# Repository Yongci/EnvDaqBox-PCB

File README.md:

# EnvDaQ Box

This is a development board designed for automated flower watering or smart agriculture, primarily used for controlling the watering and lighting systems. It is currently under development.
The development board utilizes Espressif Systems' ESP32-C6 as the main controller. This SoC is based on the RISC-V architecture core and supports ultra-low power consumption and WiFi-6 (802.11ax).

## 3D model

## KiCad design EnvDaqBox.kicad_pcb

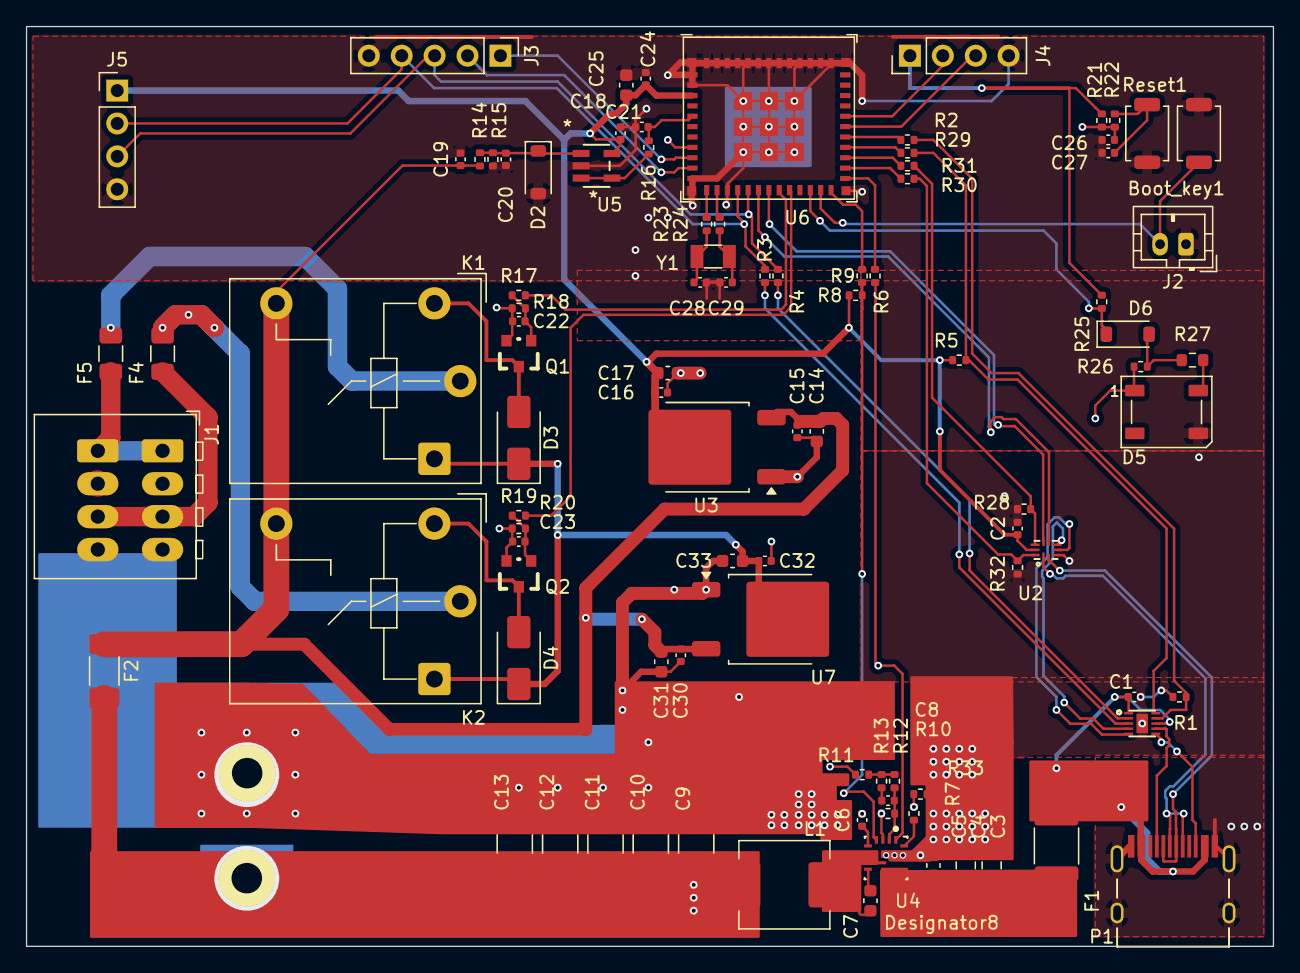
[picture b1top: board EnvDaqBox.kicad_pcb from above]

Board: 4 copper layers, 96.2 x 71.0 mm, 96 parts (0 on the bottom side), 66 nets.

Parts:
Boot_key1: SW_Push; SW_SPST_TS-1088-xR020
C1, C19: 1uF/50V(10%); C_0402_1005Metric
C2, C15, C16, C18, C20, C22, C23, C24, C27, C31, C32: 0.1uF/50V(10%); C_0402_1005Metric
C3, C4: 10uF/50V(20%); C_0805_2012Metric
C5, C7: 0.1uF/50V(10%); C_0603_1608Metric
C6: 47nF/50V(10%); C_0402_1005Metric
C8: 47pF/50V(10%); C_0402_1005Metric
C9, C10, C11, C12, C13: 22uF/25V(10%); C_1210_3225Metric
C14, C17, C25, C30, C33: 10uF/25V(20%); C_0603_1608Metric
C21: 0.1uF/6V(10%); C_0402_1005Metric
C26: 1uF; C_0402_1005Metric
C28, C29: 12pF; C_0402_1005Metric
D2: BZT52C3V3; D_SOD-123
D3, D4: 1N4007; D_SMA
D5: WS2812B; LED_WS2812B_PLCC4_5.0x5.0mm_P3.2mm
D6: 1N4148W; D_SOD-123
F1: 5A/33V; Fuse_1812_4532Metric
F2: 15A; C_1808_4520Metric
F4, F5: 5A/16V; Fuse_1206_3216Metric
J1: Screw_Terminal_01x04; TerminalBlock_WAGO_233-504_2x04_P2.54mm
J2: Conn_01x02_Pin; JST_PH_B2B-PH-K_1x02_P2.00mm_Vertical
J3: Conn_01x05_Pin; PinHeader_1x05_P2.54mm_Vertical
J4, J5: Conn_01x04_Pin; PinHeader_1x04_P2.54mm_Vertical
K1, K2: JQC-3FF-005-1H; Relay_SPST_Hongfa_JQC-3FF_0XX-1H
L1: 5.6uH; L_APV_APH0650
P1: TYPE-C-Receptacle-2.0
Q1, Q2: S8050; SOT-23
R1: 56k(1%); R_0402_1005Metric
R2, R3, R4, R6, R9, R11, R13, R22, R29, R30, R31, R33: 0; R_0402_1005Metric
R5, R8, R21, R28, R32: 10k; R_0402_1005Metric
R7: 52.3k(1%); R_0402_1005Metric
R10: 20k(1%); R_0402_1005Metric
R12: 400k(1%); R_0402_1005Metric
R14: 120k(1%); R_0402_1005Metric
R15: 43k(1%); R_0402_1005Metric
R16, R17, R19: 1k(1%); R_0402_1005Metric
R18, R20: 5.1k(1%); R_0402_1005Metric
R23, R24: 0(1%); R_0402_1005Metric
R25: 3.3k(1%); R_0402_1005Metric
R26: 10k(1%); R_0402_1005Metric
R27: 0(1%); R_0603_1608Metric
Reset1: SW_Push; SW_SPST_TS-1088-xR020
U1: CH224Q; DFN10_2X2
U2: CH9442Q; QFN10_14X18
U3: SGM2212-3.3XOB2G/TR; TO-252-2
U4: TPS56A37RPAR; RPA0010A-MFG
U5: TSU111HYLT; SOT23-5_STM
U6: ESP32-C6-MINI-1U
U7: SGM2212-5.0XOB2G/TR; TO-252-2
Y1: 32kHz; Crystal_SMD_3215-2Pin_3.2x1.5mm

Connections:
/BAT_VREF: C21.2, R16.1, U6.5 (IO2)
/BUCK_EN: R6.1, U6.25 (IO19)
/BUCK_PG: R9.1, U6.24 (IO18)
/CFG1: R2.1, U6.29 (IO23)
/CH_USB_N: U1.5 (DM), U2.4 (S0B)
/CH_USB_P: U1.4 (DP), U2.5 (S0A)
/EN: R31.1, U6.27 (IO21)
/ESP32USB_N: U2.6 (S1B), U6.17 (IO12)
/ESP32USB_P: U2.7 (S1A), U6.18 (IO13)
/PD_N: P1.A7 (DM1), P1.B7 (DM2), U2.2 (XB)
/PD_P: P1.A6 (DP1), P1.B6 (DP2), U2.1 (XA)
/QO1: F5.2, J1.1
/QO2: F4.2, J1.3
/RELAY_1: R17.2, U6.19 (IO14)
/RELAY_2: R19.2, U6.20 (IO15)
/SEL: R30.1, U6.26 (IO20)
/SINK_PG: R29.1, U6.28 (IO22)
/TCK/I2C_SDA: J3.4, J5.2, R3.1, U6.15 (IO6)
/TDI: J3.2, U6.10 (IO5)
/TDO/I2C_SCL: J3.3, J5.3, R4.1, U6.16 (IO7)
/TMS: J3.1, U6.9 (IO4)
GND: Boot_key1.1, C1.2, C2.2, C3.2, C4.2, C5.2, C9.2, C10.2, C11.2, C12.2, C13.2, C14.2, C15.2, C16.2, C17.2, C18.2, C19.2, C20.2, C21.1, C22.2, C23.2, C24.2, C25.2, C26.2, C27.2, C28.2, C29.2, C30.2, C31.2, C32.2, C33.2, D2.2 (A), D5.3 (VSS), J1.2, J1.4, J2.1, J3.5, J4.4, J5.4, P1.0, P1.A1 (GND), P1.B1 (GND), Q1.2 (E), Q2.2 (E), R1.1, R15.2, R18.2, R20.2, R28.2, R32.2, R33.1, Reset1.1, U1.0 (GND), U2.3 (GND), U3.1 (GND), U4.9 (PGND), U5.2 (VCC-), U6.1 (GND), U6.2 (GND), U6.11 (GND), U6.14 (GND), U6.36 (GND), U6.37 (GND), U6.38 (GND), U6.39 (GND), U6.40 (GND), U6.41 (GND), U6.42 (GND), U6.43 (GND), U6.44 (GND), U6.45 (GND), U6.46 (GND), U6.47 (GND), U6.48 (GND), U6.49 (GND), U6.50 (GND), U6.51 (GND), U6.52 (GND), U6.53 (GND), U7.1 (GND)
GNDA: C6.2, R7.2, R10.2, R33.2, U4.3 (AGND)
unnamed: C8.1, R13.1
unnamed: C9.1, C10.1, C11.1, C12.1, C13.1, F2.2, L1.2, R11.1
unnamed: C27.1, R22.2, Reset1.2
unnamed: C28.1, R23.2, Y1.2
unnamed: C29.1, R24.2, Y1.1
unnamed: C20.1, D2.1 (K), R14.2, R15.1, U5.1 (IN1+)
unnamed: D3.2 (A), K1.A2, Q1.3 (C)
unnamed: D4.2 (A), K2.A2, Q2.3 (C)
unnamed: D5.4 (DIN), R27.2
unnamed: D6.2 (A), R26.1, R27.1
unnamed: D6.1 (K), R25.1, U6.22 (IO8)
unnamed: F4.1, K2.13
unnamed: F5.1, K1.13
unnamed: Boot_key1.2, J2.2, U6.23 (IO9)
unnamed: J4.2, U6.31 (TXD0)
unnamed: J4.3, U6.30 (RXD0)
unnamed: P1.A5 (CC1), U1.7 (CC1)
unnamed: P1.B5 (CC2), U1.6 (CC2)
unnamed: C22.1, Q1.1 (B), R17.1, R18.1
unnamed: C23.1, Q2.1 (B), R19.1, R20.1
unnamed: R11.2, R12.1, R13.2
unnamed: R1.2, R2.2, U1.9 (CFG1)
unnamed: R4.2, U1.2 (CFG2/SCL)
unnamed: R3.2, U1.3 (CFG3/SDA)
unnamed: R5.2, R29.2, U1.10 (PG)
unnamed: R28.1, R31.2, U2.8 (EN#)
unnamed: R30.2, R32.1, U2.10 (SEL)
unnamed: C7.1, U4.7 (BOOT)
unnamed: R6.2, U4.1 (EN)
unnamed: C8.2, R10.1, R12.2, U4.2 (FB)
unnamed: R7.1, U4.10 (MODE)
unnamed: R8.1, R9.2, U4.4 (PG)
unnamed: C6.1, U4.5 (SS)
unnamed: C7.2, L1.1, U4.6 (SW)
unnamed: C3.1, C4.1, C5.1, F1.1, U4.8 (VIN)
unnamed: R16.2, U5.3 (IN-), U5.4 (OUT)
unnamed: C26.1, R21.2, R22.1, U6.8 (EN)
unnamed: R23.1, U6.12 (IO0)
unnamed: R24.1, U6.13 (IO1)
VBUS: C1.1, F1.2, P1.A4 (VBUS), P1.B4 (VBUS), U1.1 (VHV), U1.8 (VBUS)
VCC_3V3: C2.1, C16.1, C17.1, C18.1, C24.1, C25.1, J4.1, J5.1, R5.1, R8.2, R21.1, R25.2, U2.9 (VCC), U3.2 (OUT), U5.5 (VCC+), U6.3 (3V3)
VCC_5V: C32.1, C33.1, D3.1 (K), D4.1 (K), D5.1 (VDD), K1.A1, K2.A1, R26.2, U7.2 (OUT)
VCC_12V: C14.1, C15.1, C19.1, C30.1, C31.1, F2.1, K1.14, K2.14, R14.1, U3.3 (IN), U7.3 (IN)

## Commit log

2026-05-08 v0.0.1
2026-05-08 v0.0.1 tag
2026-05-08 DRC check
